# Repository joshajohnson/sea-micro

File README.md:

# sea-micro

An Arduino Pro Micro, with but with a Type-C connector.

Targeted as an alternative for the ubiquitous Pro Micro in DIY keyboard applications.

Features:
- Pro Micro compatible pinout.
- Mid Mount USB Type-C Connector.
- On-board reset button.

Developed in conjunction with [Custom KBD](customkbd.com).

Revision History:

0.1 - "Elite-C" compatible pinout, with added ESD protection.

0.2 - Removes castellated pads for lower cost manufacturing.

0.3 - Name changed to sea-micro, now targeting Pro Micro w/ Type-C feature set at the lowest cost possible.

0.4 - Added D+ and D- pads on underside of PCB, DFM improvements for USB connector.

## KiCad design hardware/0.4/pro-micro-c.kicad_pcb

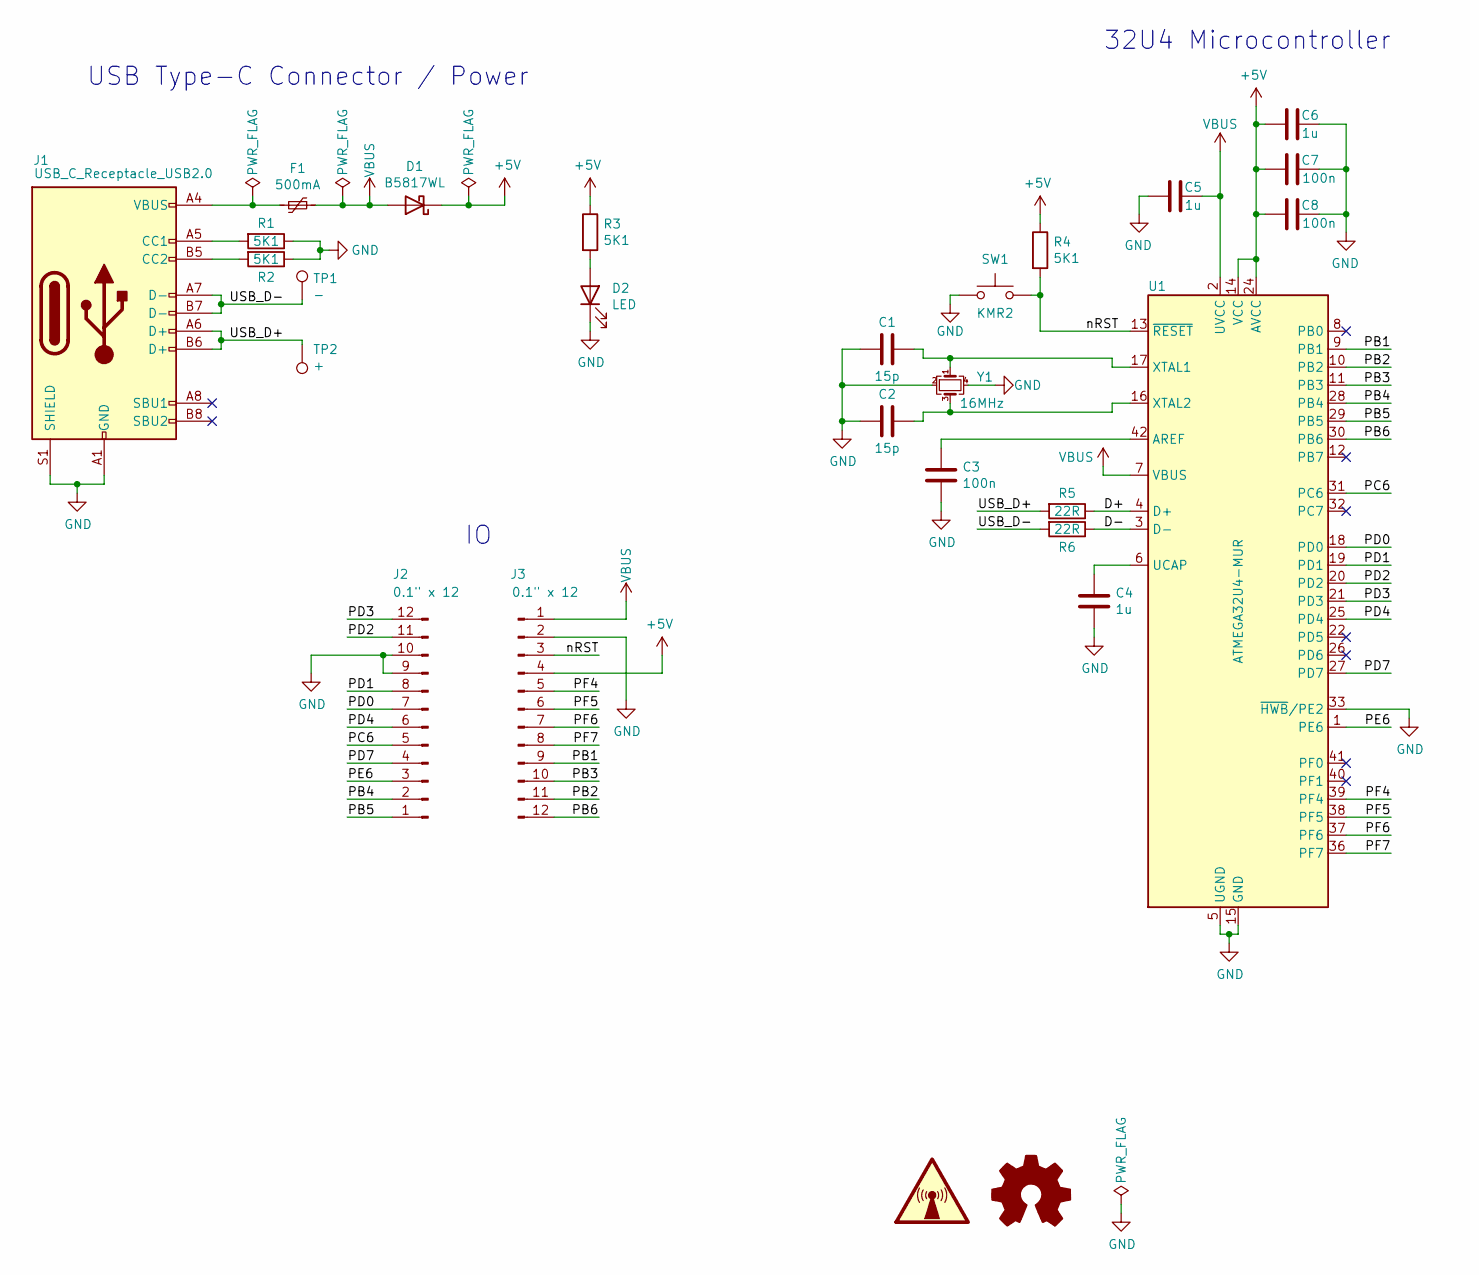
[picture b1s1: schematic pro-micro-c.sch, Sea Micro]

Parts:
C1, C2: 15p; C_0603_1608Metric; MPN CL10C150JB8NNNC; LCSC C1644
C3, C7, C8: 100n; C_0603_1608Metric; MPN CL10B104KO8NNNC; LCSC C66501
C4, C5, C6: 1u; C_0603_1608Metric; MPN CL10A105KO8NNNC; LCSC C1592
D1: B5817WL; D_SOD-123F; MPN B5817WL; LCSC C122853
D2: LED; LED_0603_1608Metric; MPN OSK40603C1E; LCSC C268294
F1: 500mA; Fuse_0603_1608Metric; MPN MF-FSMF050X-2; LCSC C210357
J1: USB_C_Receptacle_USB2.0; USB_C_TYPE-C-31-M-14; MPN TYPE-C-31-M-14; LCSC C223907
J2, J3: 0.1\" x 12; Castellated_Short_P2.54x12
LOGO1: Logo_Open_Hardware_Small; OSHW_Logo_3.6x3.6_F.Mask
R1, R2, R3, R4: 5K1; R_0603_1608Metric; MPN RC0603JR-075K1L; LCSC C14677
R5, R6: 22R; R_0603_1608Metric; MPN RC0603JR-0722RL; LCSC C108405
SW1: KMR2; SW_Push_KMR2; MPN TS-1185EC-C-D-B; LCSC C318893
SYM1: SYM_Radio_Waves_Large; sea-micro-silk
TP1: -; TestPoint_Pad_D1.5mm
TP2: +; TestPoint_Pad_D1.5mm
U1: ATMEGA32U4-MUR; QFN-44-1EP_7x7mm_P0.5mm_EP5.2x5.2mm; MPN ATMEGA32U4-MUR; LCSC C45874
Y1: 16MHz; Crystal_SMD_3225-4Pin_3.2x2.5mm; MPN TAXM16M4RDBCCT2T; LCSC C164044

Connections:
+5V: C6.1, C7.1, C8.1, D1.1 (K), J3.4, R3.1, R4.1, U1.14 (VCC), U1.24 (AVCC), U1.34 (VCC), U1.44 (AVCC)
/D+: R5.1, U1.4 (D+)
/D-: R6.1, U1.3 (D-)
/PB1: J3.9, U1.9 (PB1)
/PB2: J3.11, U1.10 (PB2)
/PB3: J3.10, U1.11 (PB3)
/PB4: J2.2, U1.28 (PB4)
/PB5: J2.1, U1.29 (PB5)
/PB6: J3.12, U1.30 (PB6)
/PC6: J2.5, U1.31 (PC6)
/PD0: J2.7, U1.18 (PD0)
/PD1: J2.8, U1.19 (PD1)
/PD2: J2.11, U1.20 (PD2)
/PD3: J2.12, U1.21 (PD3)
/PD4: J2.6, U1.25 (PD4)
/PD7: J2.4, U1.27 (PD7)
/PE6: J2.3, U1.1 (PE6)
/PF4: J3.5, U1.39 (PF4)
/PF5: J3.6, U1.38 (PF5)
/PF6: J3.7, U1.37 (PF6)
/PF7: J3.8, U1.36 (PF7)
/USB_D+: J1.A6 (D+), J1.B6 (D+), R5.2, TP2.1
/USB_D-: J1.A7 (D-), J1.B7 (D-), R6.2, TP1.1
/nRST: J3.3, R4.2, SW1.2, U1.13 (~RESET)
GND: C1.2, C2.2, C3.2, C4.2, C5.1, C6.2, C7.2, C8.2, D2.1 (K), J1.A1 (GND), J1.A12 (GND), J1.B1 (GND), J1.B12 (GND), J1.S1 (SHIELD), J2.9, J2.10, J3.2, R1.1, R2.1, SW1.1, U1.5 (UGND), U1.15 (GND), U1.23 (GND), U1.33 (~HWB~/PE2), U1.35 (GND), U1.43 (GND), U1.45 (GND), Y1.2, Y1.4
unnamed: C1.1, U1.17 (XTAL1), Y1.1
unnamed: C2.1, U1.16 (XTAL2), Y1.3
unnamed: C3.1, U1.42 (AREF)
unnamed: C4.1, U1.6 (UCAP)
unnamed: D2.2 (A), R3.2
unnamed: F1.2, J1.A4 (VBUS), J1.A9 (VBUS), J1.B4 (VBUS), J1.B9 (VBUS)
unnamed: J1.A5 (CC1), R1.2
unnamed: J1.B5 (CC2), R2.2
VBUS: C5.2, D1.2 (A), F1.1, J3.1, U1.2 (UVCC), U1.7 (VBUS)

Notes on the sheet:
32U4 Microcontroller
USB Type-C Connector / Power

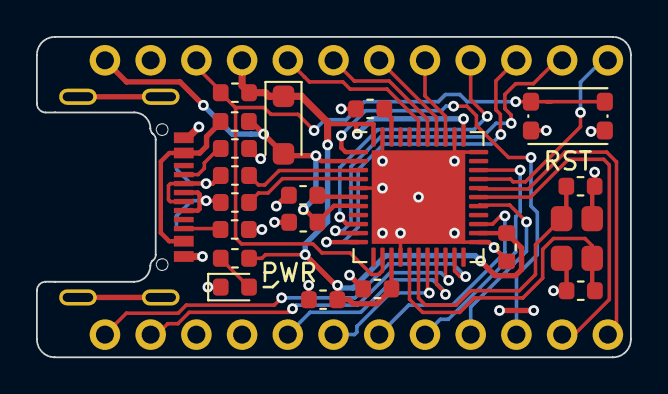
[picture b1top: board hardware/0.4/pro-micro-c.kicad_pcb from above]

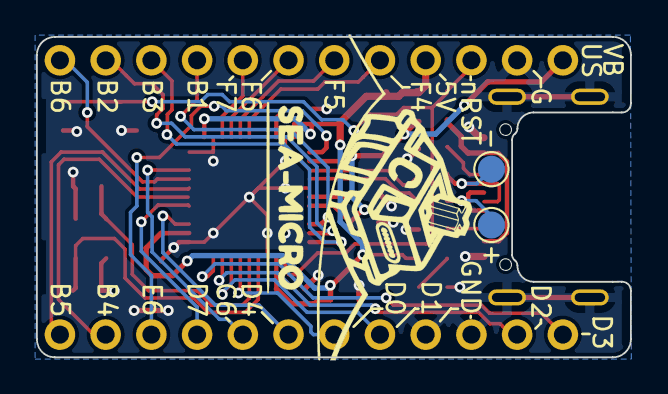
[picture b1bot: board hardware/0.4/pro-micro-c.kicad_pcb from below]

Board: 2 copper layers, 33.0 x 17.8 mm, 27 parts (4 on the bottom side), 34 nets.

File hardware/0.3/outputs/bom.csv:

Reference, Quantity, Value, Footprint, MPN , Manufacturer, LCSC
C1 C2 ,2,15p,Capacitor_SMD:C_0603_1608Metric,CL10C150JB8NNNC,Samsung Electro-Mechanics,C1644
C6 C4 C5 ,3,1u,Capacitor_SMD:C_0603_1608Metric,CL10A105KO8NNNC,Samsung Electro-Mechanics,C1592
C8 C7 C3 ,3,100n,Capacitor_SMD:C_0603_1608Metric,CL10B104KO8NNNC,Samsung Electro-Mechanics,C66501
D1 ,1,B5817WL,josh-passives-smt:D_SOD-123F,B5817WL,Shikues,C122853
D2 ,1,LED,LED_SMD:LED_0603_1608Metric,OSK40603C1E,OptoSupply,C268294
F1 ,1,500mA,josh-passives-smt:Fuse_0603_1608Metric,MF-FSMF050X-2,BOURNS,C210357
J1 ,1,USB_C_Receptacle_USB2.0,josh-connectors:USB_C_TYPE-C-31-M-14,TYPE-C-31-M-14,Korean Hroparts Elec,C223907
R1 R2 R4 R3 ,4,5K1,Resistor_SMD:R_0603_1608Metric,RC0603JR-075K1L,YAGEO,C14677
R5 R6 ,2,22R,Resistor_SMD:R_0603_1608Metric,RC0603JR-0722RL,YAGEO,C108405
SW1 ,1,KMR2,josh-buttons-switches:SW_Push_KMR2,TS-1185EC-C-D-B,XKB Connectivity,C318893
U1 ,1,ATMEGA32U4-MUR,Package_DFN_QFN:QFN-44-1EP_7x7mm_P0.5mm_EP5.2x5.2mm,ATMEGA32U4-MUR,Microchip/Atmel,C45874
Y1 ,1,16MHz,josh-oscillators:Crystal_SMD_3225-4Pin_3.2x2.5mm,TAXM16M4RDBCCT2T,TAE(Zhejiang Abel Elec),C164044

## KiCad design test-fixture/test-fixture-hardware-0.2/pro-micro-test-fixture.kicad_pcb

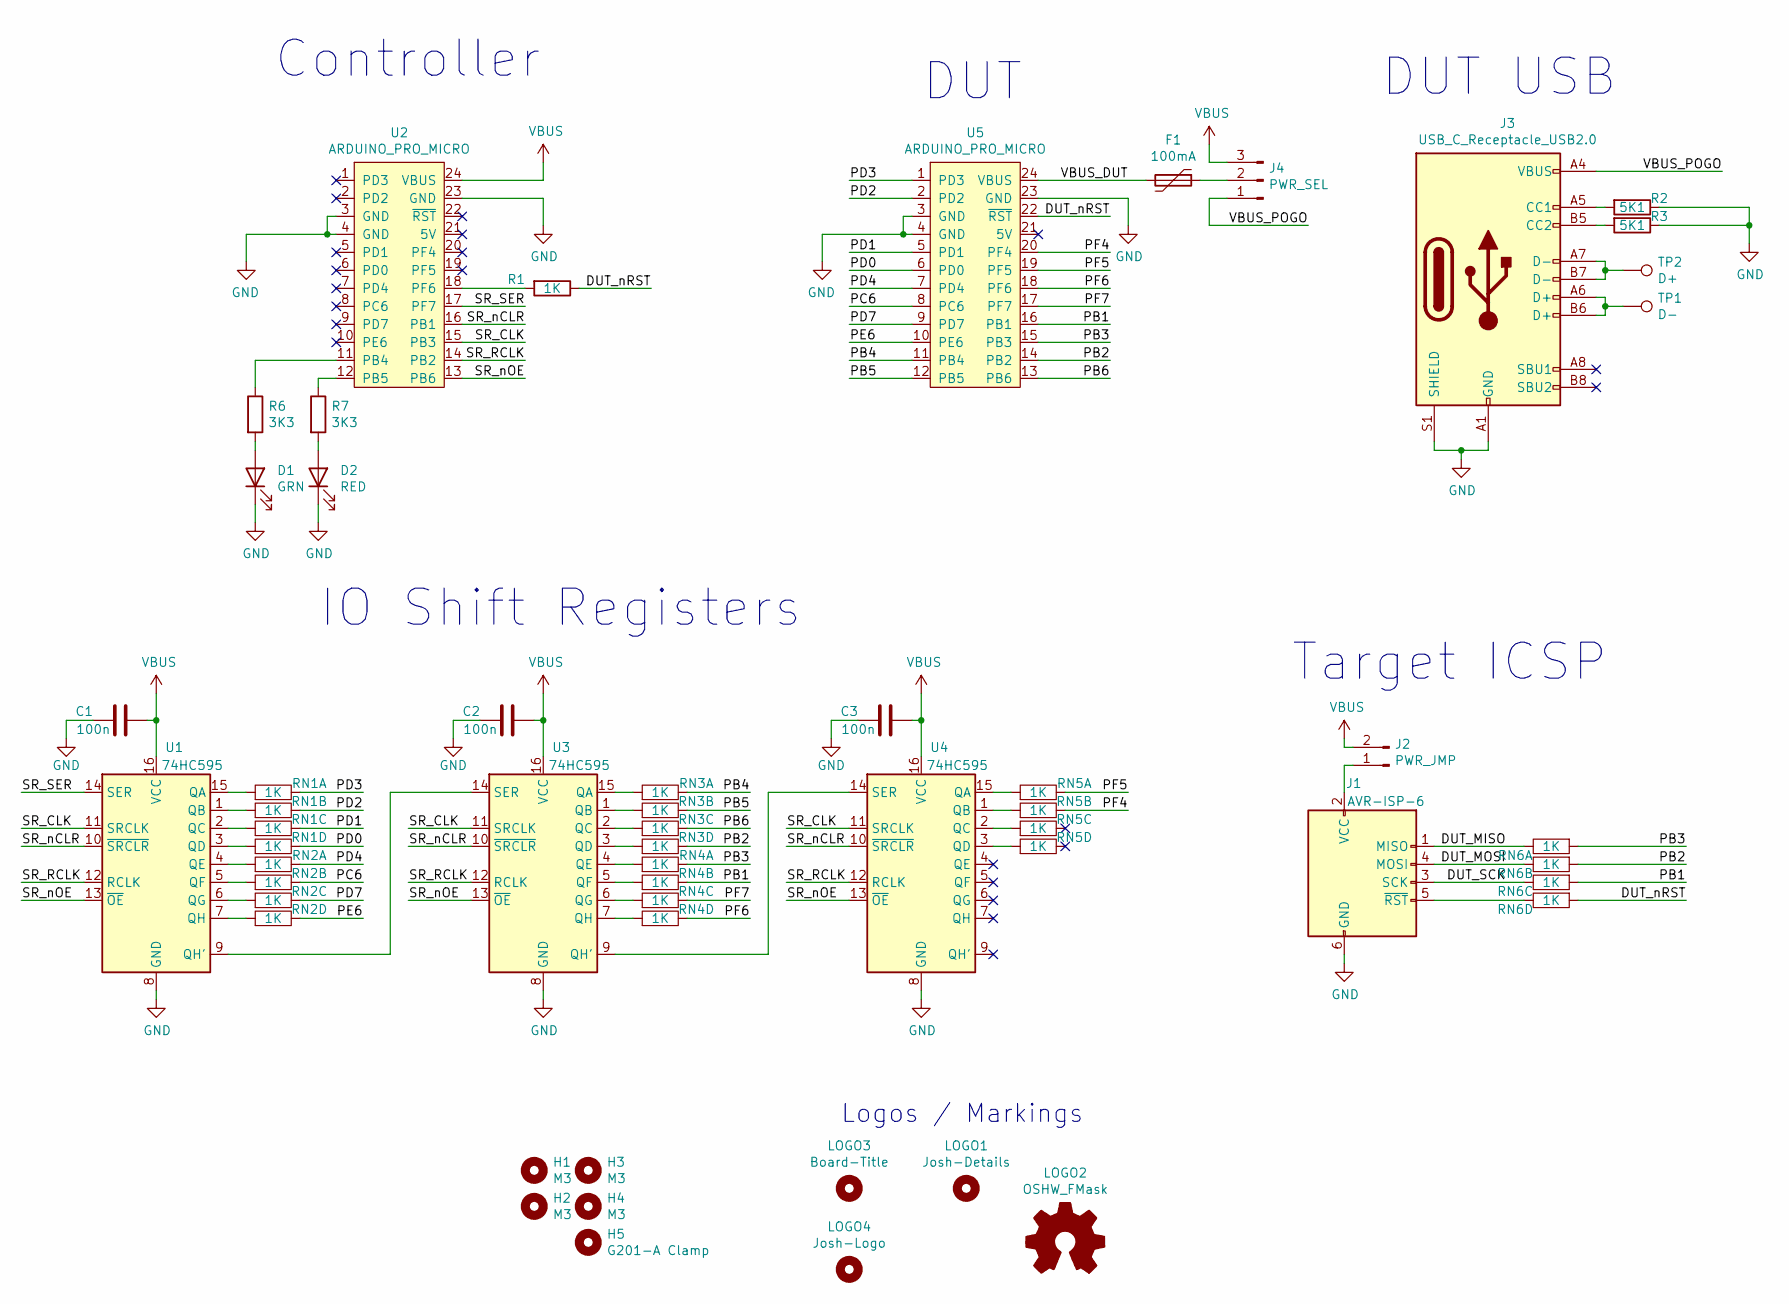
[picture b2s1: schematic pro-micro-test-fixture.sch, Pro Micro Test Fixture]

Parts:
C1, C2, C3: 100n; C_0603_1608Metric
D1: GRN; LED_0603_1608Metric
D2: RED; LED_0603_1608Metric
F1: 100mA; Fuse_0603_1608Metric
H1, H2, H3, H4: M3; MountingHole_3.2mm_M3_Pad
H5: G201-A Clamp; GH-201A
J1: AVR-ISP-6; IDC-Header_2x03_P2.54mm_Vertical
J2: PWR_JMP; PinHeader_1x02_P2.54mm_Vertical
J3: USB_C_Receptacle_USB2.0; USB_C_U262-161N-4BVC11
J4: PWR_SEL; PinHeader_1x03_P2.54mm_Horizontal
LOGO1: Josh-Details; josh-details
LOGO2: OSHW_FMask; OSHW_Logo_3.6x3.6_F.Mask
LOGO3: Board-Title; board-title
LOGO4: Josh-Logo; josh-johnson-logo-8_6x1_5
R1: 1K; R_0603_1608Metric
R2, R3: 5K1; R_0603_1608Metric
R6, R7: 3K3; R_0603_1608Metric
RN1, RN2, RN3, RN4, RN5, RN6: 1K; R_Array_Convex_4x0603
TP1: D-; TestPoint_Loop_D2.60mm_Drill1.4mm_Beaded
TP2: D+; TestPoint_Loop_D2.60mm_Drill1.4mm_Beaded
U1, U3, U4: 74HC595; SOIC-16_3.9x9.9mm_P1.27mm
U2: ARDUINO_PRO_MICRO; Arduino_Pro_Micro
U5: ARDUINO_PRO_MICRO; Arduino_Pro_Micro_POGO

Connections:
/DUT_MISO: J1.1 (MISO), RN6.5
/DUT_MOSI: J1.4 (MOSI), RN6.6
/DUT_SCK: J1.3 (SCK), RN6.7
/DUT_nRST: R1.1, RN6.1, U5.22 (~RST)
/PB1: RN4.6, RN6.2, U5.16 (PB1)
/PB2: RN3.8, RN6.3, U5.14 (PB2)
/PB3: RN4.5, RN6.4, U5.15 (PB3)
/PB4: RN3.5, U5.11 (PB4)
/PB5: RN3.6, U5.12 (PB5)
/PB6: RN3.7, U5.13 (PB6)
/PC6: RN2.6, U5.8 (PC6)
/PD0: RN1.8, U5.6 (PD0)
/PD1: RN1.7, U5.5 (PD1)
/PD2: RN1.6, U5.2 (PD2)
/PD3: RN1.5, U5.1 (PD3)
/PD4: RN2.5, U5.7 (PD4)
/PD7: RN2.7, U5.9 (PD7)
/PE6: RN2.8, U5.10 (PE6)
/PF4: RN5.6, U5.20 (PF4)
/PF5: RN5.5, U5.19 (PF5)
/PF6: RN4.8, U5.18 (PF6)
/PF7: RN4.7, U5.17 (PF7)
/SR_CLK: U1.11 (SRCLK), U2.15 (PB3), U3.11 (SRCLK), U4.11 (SRCLK)
/SR_RCLK: U1.12 (RCLK), U2.14 (PB2), U3.12 (RCLK), U4.12 (RCLK)
/SR_SER: U1.14 (SER), U2.17 (PF7)
/SR_nCLR: U1.10 (~SRCLR), U2.16 (PB1), U3.10 (~SRCLR), U4.10 (~SRCLR)
/SR_nOE: U1.13 (~OE), U2.13 (PB6), U3.13 (~OE), U4.13 (~OE)
/VBUS_DUT: F1.2, U5.24 (VBUS)
/VBUS_POGO: J3.A4 (VBUS), J3.A9 (VBUS), J3.B4 (VBUS), J3.B9 (VBUS), J4.1
GND: C1.2, C2.2, C3.2, D1.1 (K), D2.1 (K), J1.6 (GND), J3.A1 (GND), J3.A12 (GND), J3.B1 (GND), J3.B12 (GND), J3.S1 (SHIELD), R2.1, R3.1, U1.8 (GND), U2.3 (GND), U2.4 (GND), U2.23 (GND), U3.8 (GND), U4.8 (GND), U5.3 (GND), U5.4 (GND), U5.23 (GND)
unnamed: D1.2 (A), R6.2
unnamed: D2.2 (A), R7.2
unnamed: F1.1, J4.2
unnamed: J1.2 (VCC), J2.1
unnamed: J1.5 (~RST), RN6.8
unnamed: J3.A5 (CC1), R2.2
unnamed: J3.A6 (D+), J3.B6 (D+), TP1.1
unnamed: J3.A7 (D-), J3.B7 (D-), TP2.1
unnamed: J3.B5 (CC2), R3.2
unnamed: R1.2, U2.18 (PF6)
unnamed: R6.1, U2.11 (PB4)
unnamed: R7.1, U2.12 (PB5)
unnamed: RN1.1, U1.3 (QD)
unnamed: RN1.2, U1.2 (QC)
unnamed: RN1.3, U1.1 (QB)
unnamed: RN1.4, U1.15 (QA)
unnamed: RN2.1, U1.7 (QH)
unnamed: RN2.2, U1.6 (QG)
unnamed: RN2.3, U1.5 (QF)
unnamed: RN2.4, U1.4 (QE)
unnamed: RN3.1, U3.3 (QD)
unnamed: RN3.2, U3.2 (QC)
unnamed: RN3.3, U3.1 (QB)
unnamed: RN3.4, U3.15 (QA)
unnamed: RN4.1, U3.7 (QH)
unnamed: RN4.2, U3.6 (QG)
unnamed: RN4.3, U3.5 (QF)
unnamed: RN4.4, U3.4 (QE)
unnamed: RN5.1, U4.3 (QD)
unnamed: RN5.2, U4.2 (QC)
unnamed: RN5.3, U4.1 (QB)
unnamed: RN5.4, U4.15 (QA)
unnamed: U1.9 (QH'), U3.14 (SER)
unnamed: U3.9 (QH'), U4.14 (SER)
VBUS: C1.1, C2.1, C3.1, J2.2, J4.3, U1.16 (VCC), U2.24 (VBUS), U3.16 (VCC), U4.16 (VCC)

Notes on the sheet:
Logos / Markings
Controller
DUT
IO Shift Registers
Target ICSP
DUT USB

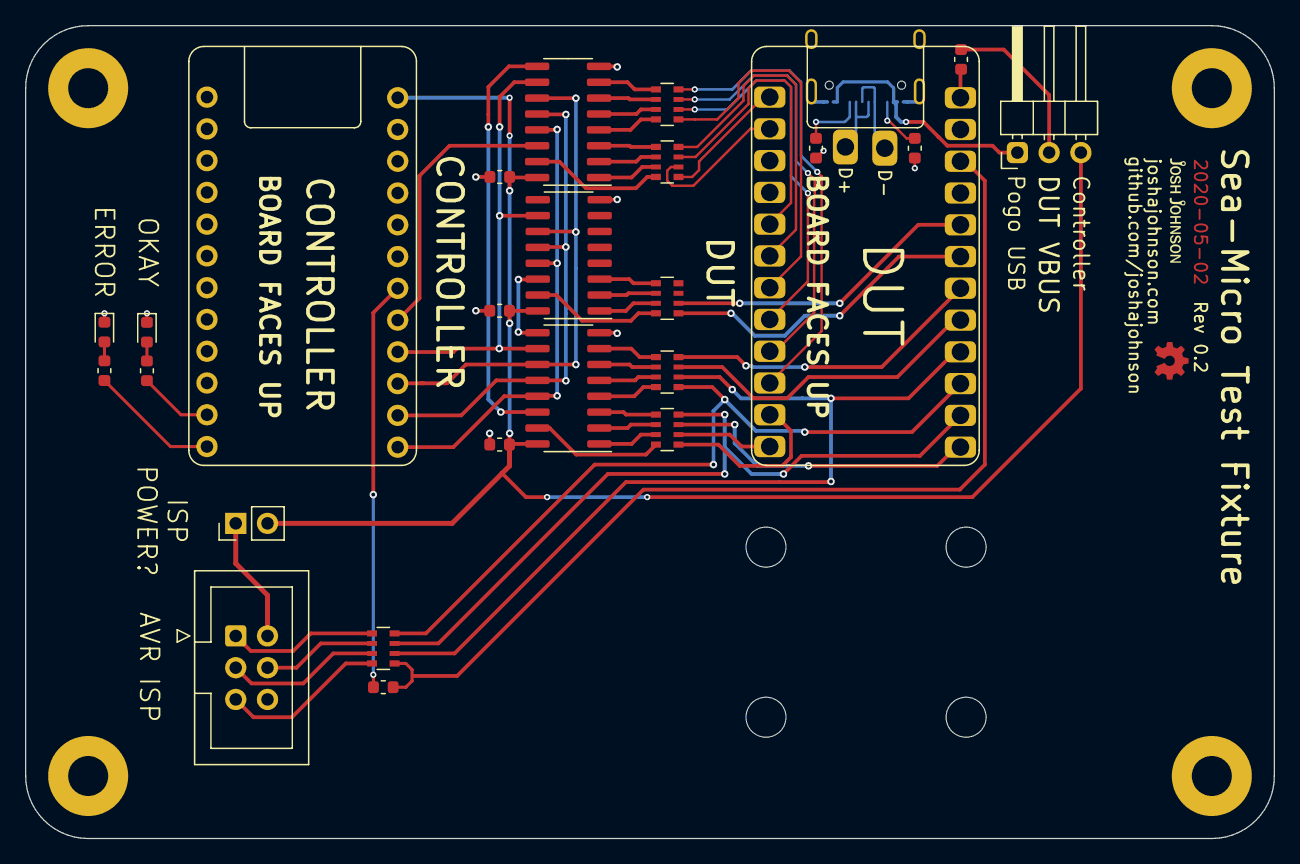
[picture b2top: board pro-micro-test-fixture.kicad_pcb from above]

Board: 2 copper layers, 99.8 x 65.0 mm, 39 parts (1 on the bottom side), 65 nets.

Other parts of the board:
LOGO2#2: OSHW_FMask; OSHW_Logo_3.6x3.6_F.Mask
LOGO3#2: Board-Title; board-title

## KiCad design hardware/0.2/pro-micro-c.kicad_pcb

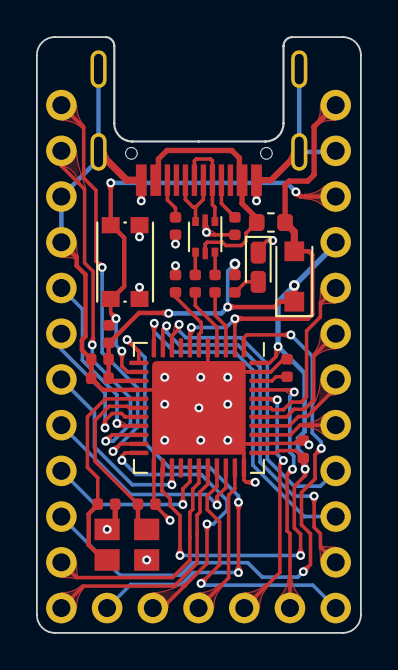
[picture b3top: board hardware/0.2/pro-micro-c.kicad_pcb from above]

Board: 2 copper layers, 18.0 x 33.1 mm, 24 parts (0 on the bottom side), 41 nets.

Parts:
C1, C2: 22p; C_0402_1005Metric
C3, C6, C7: 100n; C_0402_1005Metric
C4, C5: 1u; C_0402_1005Metric
D1: D_Schottky; D_SOD-123F
D2: LED; LED_0603_1608Metric_Castellated
F1: 500mA; Fuse_0603_1608Metric
J1: USB_C_Receptacle_USB2.0; USB_C_TYPE-C-31-M-14
J2, J4: 0.1" x 12; Castellated_Short_P2.54x12
J3: 0.1" x 5; Castellated_Short_2.54x5
R1, R2: 5K1; R_0402_1005Metric
R3: 10K; R_0402_1005Metric
R4: 2K2; R_0402_1005Metric
R5, R6: 22R; R_0402_1005Metric
SW1: SW_Push; SW_Push_1P1T_NO_CK_KMR2
U1: USBLC6-2P6; SOT-666
U2: ATmega32U4-MU; QFN-44-1EP_7x7mm_P0.5mm_EP5.2x5.2mm
Y1: 16MHz; Crystal_SMD_3225-4Pin_3.2x2.5mm

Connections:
+5V: C5.1, C6.1, C7.1, D1.1, J4.4, R3.1, R4.1, U2.14, U2.24, U2.34, U2.44
/D+: R5.1, U2.4
/D-: R6.1, U2.3
/PB1: J4.9, U2.9
/PB2: J4.11, U2.10
/PB3: J4.10, U2.11
/PB4: J2.2, U2.28
/PB5: J2.1, U2.29
/PB6: J4.12, U2.30
/PB7: J3.5, U2.12
/PC6: J2.5, U2.31
/PC7: J3.3, U2.32
/PD0: J2.7, U2.18
/PD1: J2.8, U2.19
/PD2: J2.11, U2.20
/PD3: J2.12, U2.21
/PD4: J2.6, U2.25
/PD5: J3.4, U2.22
/PD7: J2.4, U2.27
/PE6: J2.3, U2.1
/PF0: J3.1, U2.41
/PF1: J3.2, U2.40
/PF4: J4.5, U2.39
/PF5: J4.6, U2.38
/PF6: J4.7, U2.37
/PF7: J4.8, U2.36
/USB_D+: R5.2, U1.4
/USB_D-: R6.2, U1.6
/nRST: J4.3, R3.2, SW1.2, U2.13
GND: C1.2, C2.2, C3.2, C4.2, C5.2, C6.2, C7.2, D2.1, J1.A1, J1.A12, J1.B1, J1.B12, J1.S1, J2.9, J2.10, J4.2, R1.1, R2.1, SW1.1, U1.2, U2.5, U2.15, U2.23, U2.33, U2.35, U2.43, U2.45, Y1.2, Y1.4
unnamed: C1.1, U2.17, Y1.1
unnamed: C2.1, U2.16, Y1.3
unnamed: C3.1, U2.42
unnamed: C4.1, U2.6
unnamed: D2.2, R4.2
unnamed: F1.2, J1.A4, J1.A9, J1.B4, J1.B9, U1.5
unnamed: J1.A5, R1.2
unnamed: J1.A6, J1.B6, U1.3
unnamed: J1.A7, J1.B7, U1.1
unnamed: J1.B5, R2.2
VBUS: D1.2, F1.1, J4.1, U2.2, U2.7

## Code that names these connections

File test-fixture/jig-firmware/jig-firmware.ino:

// 74HC595 Pins
#define SR_nOE  10  // B6
#define SR_SER  18  // F7
#define SR_CLK  14  // B3
#define SR_RCLK 16  // B2
#define SR_nCLR 15  // B1

// DUT Reset
#define DUT_nRST  19  // F6

// State LEDs
#define LED_OKAY  8   // B4
#define LED_ERROR 9   // B5

// Commands
#define STATE_OKAY  32
#define STATE_ERROR 33
#define STATE_RESET 34

#define HIGH_Z      128
#define HARD_RESET  255

void shift_out(uint32_t bitstream);
void press_key(uint8_t key);

void setup() 
{
  // Shift Reg
  pinMode(SR_nOE, OUTPUT);
  pinMode(SR_SER, OUTPUT);
  pinMode(SR_nCLR, OUTPUT);
  pinMode(SR_CLK, OUTPUT);
  pinMode(SR_RCLK, OUTPUT);
  // Start high Z
  digitalWrite(SR_nOE, HIGH);

  // DUT nRST start high
  pinMode(DUT_nRST, OUTPUT);
  digitalWrite(DUT_nRST, HIGH);

  // LEDs
  pinMode(LED_OKAY, OUTPUT);
  pinMode(LED_ERROR, OUTPUT);
  digitalWrite(LED_OKAY, LOW);
  digitalWrite(LED_ERROR, LOW);

  Serial.begin(115200);
}

void loop() 
{
  while (Serial.available() > 0)
  {
    uint8_t data = Serial.parseInt();

    if (data >= 1 && data <= 18)
    {
      press_key(data);
    }
    else if (data == HIGH_Z)
    {
      digitalWrite(SR_nOE, HIGH);
      digitalWrite(DUT_nRST, HIGH);
      pinMode(DUT_nRST, INPUT);
      Serial.println("High Z IO");
    }
    else if (data == STATE_OKAY)
    {
      digitalWrite(STATE_ERROR, LOW);
      digitalWrite(STATE_OKAY, HIGH);
      Serial.println("State OKAY");
    }
    else if (data == STATE_ERROR)
    {
      digitalWrite(STATE_ERROR, HIGH);
      digitalWrite(STATE_OKAY, LOW);
      Serial.println("State ERROR");
    }
    else if (data == STATE_RESET)
    {
      digitalWrite(STATE_ERROR, LOW);
      digitalWrite(STATE_OKAY, LOW);
      Serial.println("State RESET");
    }
    else if (data == HARD_RESET)
    {
      pinMode(DUT_nRST, OUTPUT);
      digitalWrite(DUT_nRST, LOW);
      delay(50);
      digitalWrite(DUT_nRST, HIGH);
      Serial.println("Hard Reset DUT");
    }
  }
}

void press_key(uint8_t key)
{
  shift_out(0xFFFFFF & ~(key - 1)); // 24 bits, active low, MSB first
  delay(50);
  shift_out(0xFFFFFF); // Release all keys
  delay(1);
  digitalWrite(SR_nOE, HIGH);

  Serial.print("Pressed Key: ");
  Serial.println(key, DEC);
}

void shift_out(uint32_t bitstream)
{
  // Shift out 24 bits, MSB first
  digitalWrite(SR_nOE, HIGH);
  shiftOut(SR_SER, SR_CLK, MSBFIRST, (bitstream & 0xFF0000) >> 16); // third byte
  shiftOut(SR_SER, SR_CLK, MSBFIRST, (bitstream & 0xFF00) >> 8);    // second byte
  shiftOut(SR_SER, SR_CLK, MSBFIRST, (bitstream & 0xFF));           // first byte
  digitalWrite(SR_nOE, LOW);
}

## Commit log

2020-01-08 layout done
2020-05-23 v0.2
2020-07-26 update files + readme
2020-12-11 all nets routed
2020-12-11 layout looking good
2020-12-11 BOM complete + cleaning up traces
2020-12-12 add silk
2020-12-13 v0.3 and test fixture off to fab
2020-12-23 test fixture sw/fw, untested
2020-12-24 test fixture working
2020-12-25 programming script improvments
2020-12-25 clean up repo inc rename
2020-12-28 add ibom pnp
2021-01-06 add pdf of schematic
2021-01-06 remove dupe
2021-01-21 update output files
2021-02-26 export 3d model
2021-06-15 Fix typos - compatible
2021-06-20 update test fixtures
2021-06-20 release 0.4
2021-06-20 update docs
2021-08-28 Fix lines at the wrong layer
2021-08-28 fix usb c connector outline
